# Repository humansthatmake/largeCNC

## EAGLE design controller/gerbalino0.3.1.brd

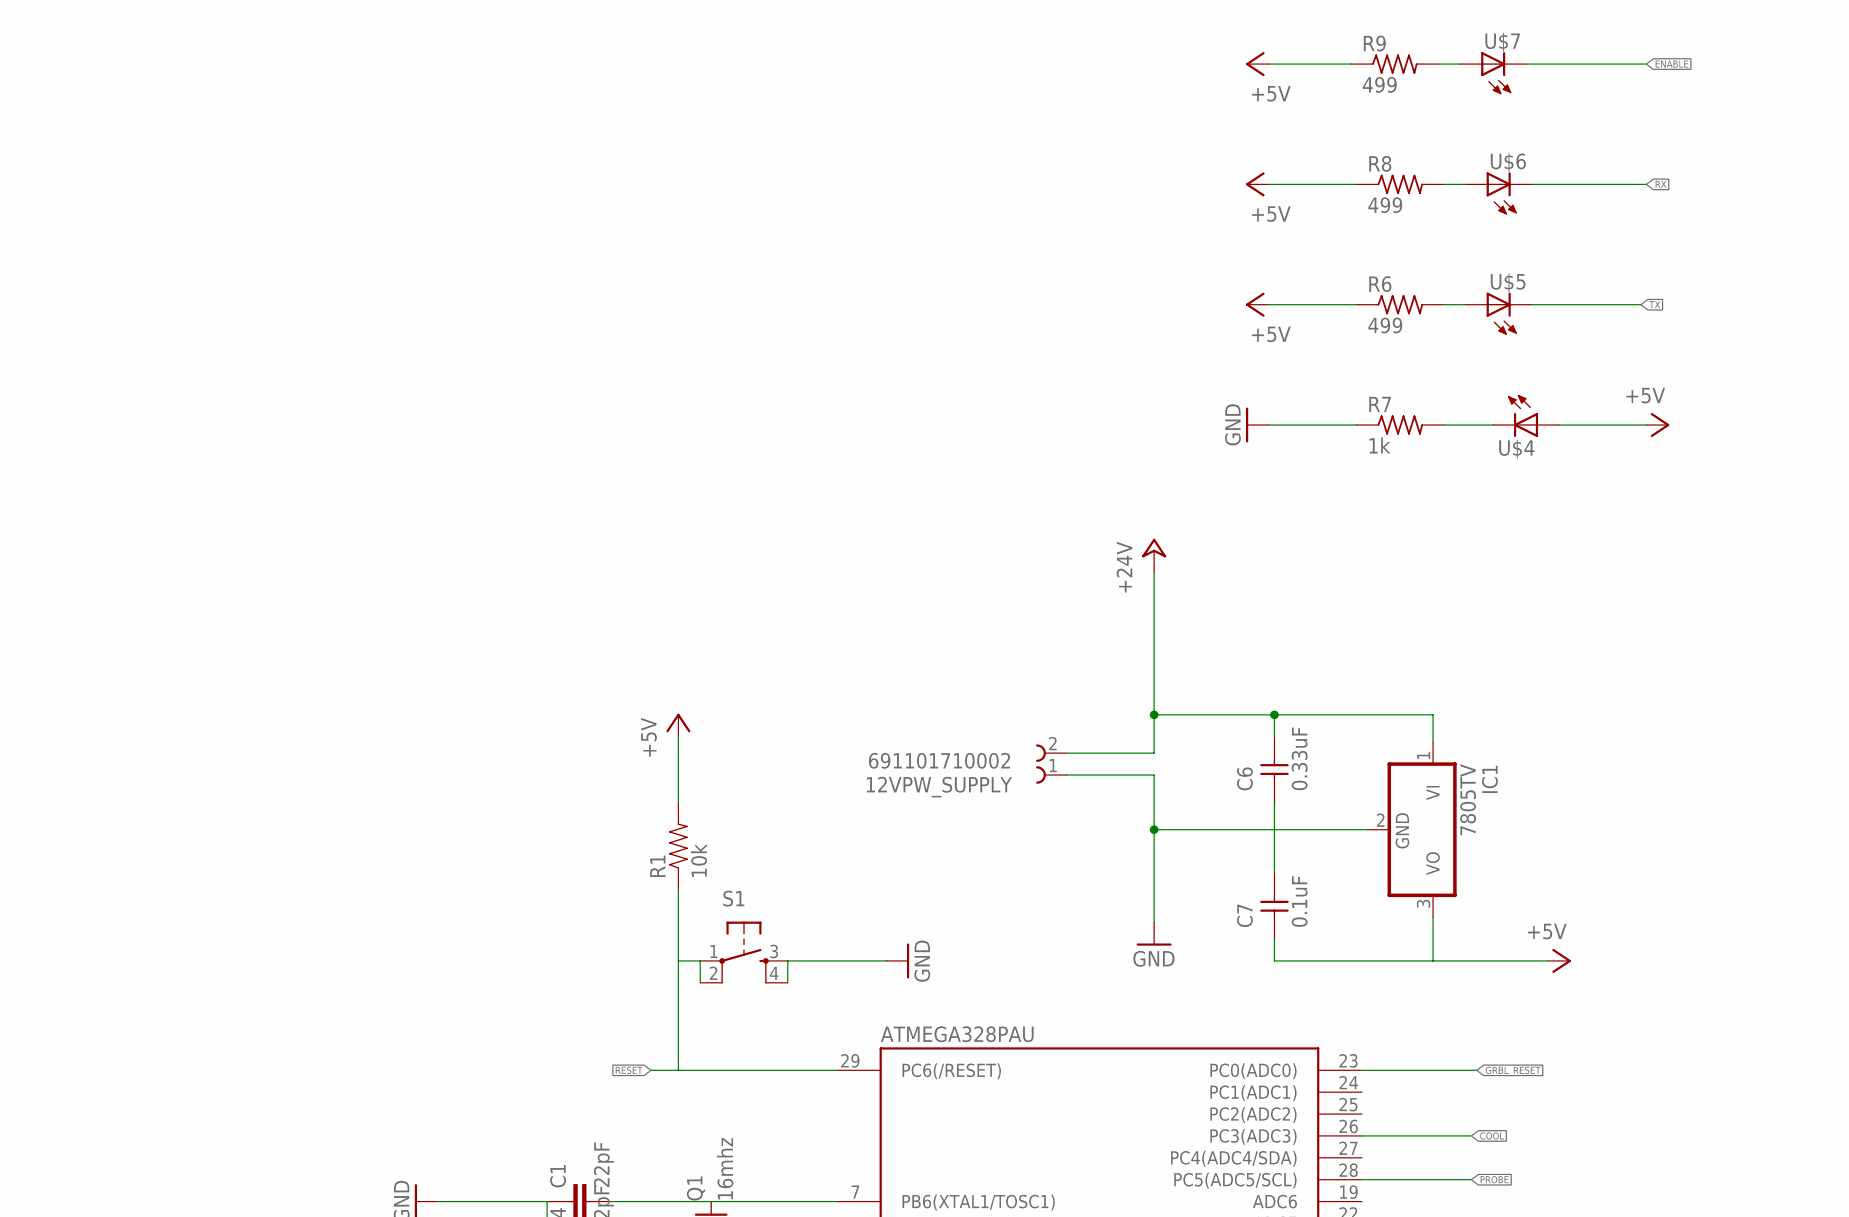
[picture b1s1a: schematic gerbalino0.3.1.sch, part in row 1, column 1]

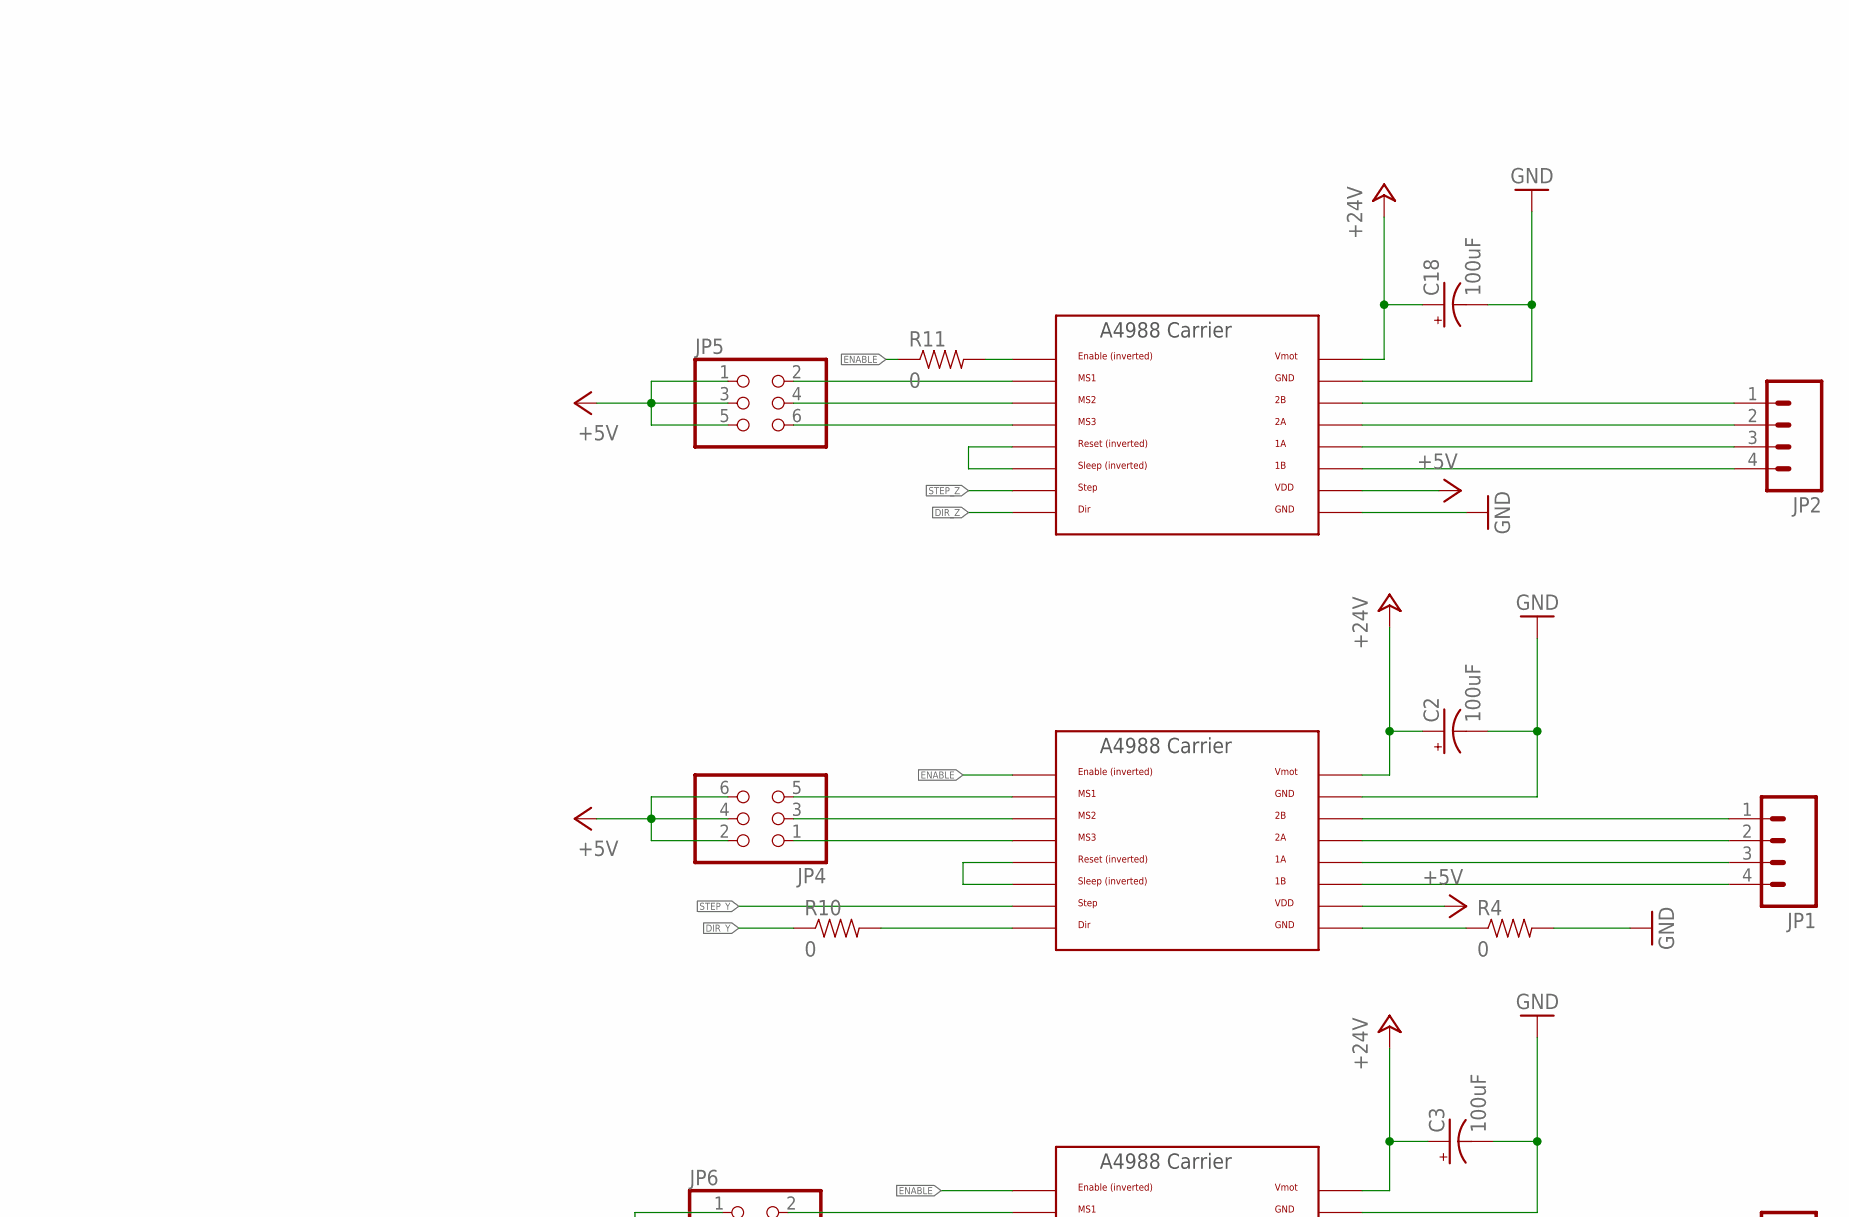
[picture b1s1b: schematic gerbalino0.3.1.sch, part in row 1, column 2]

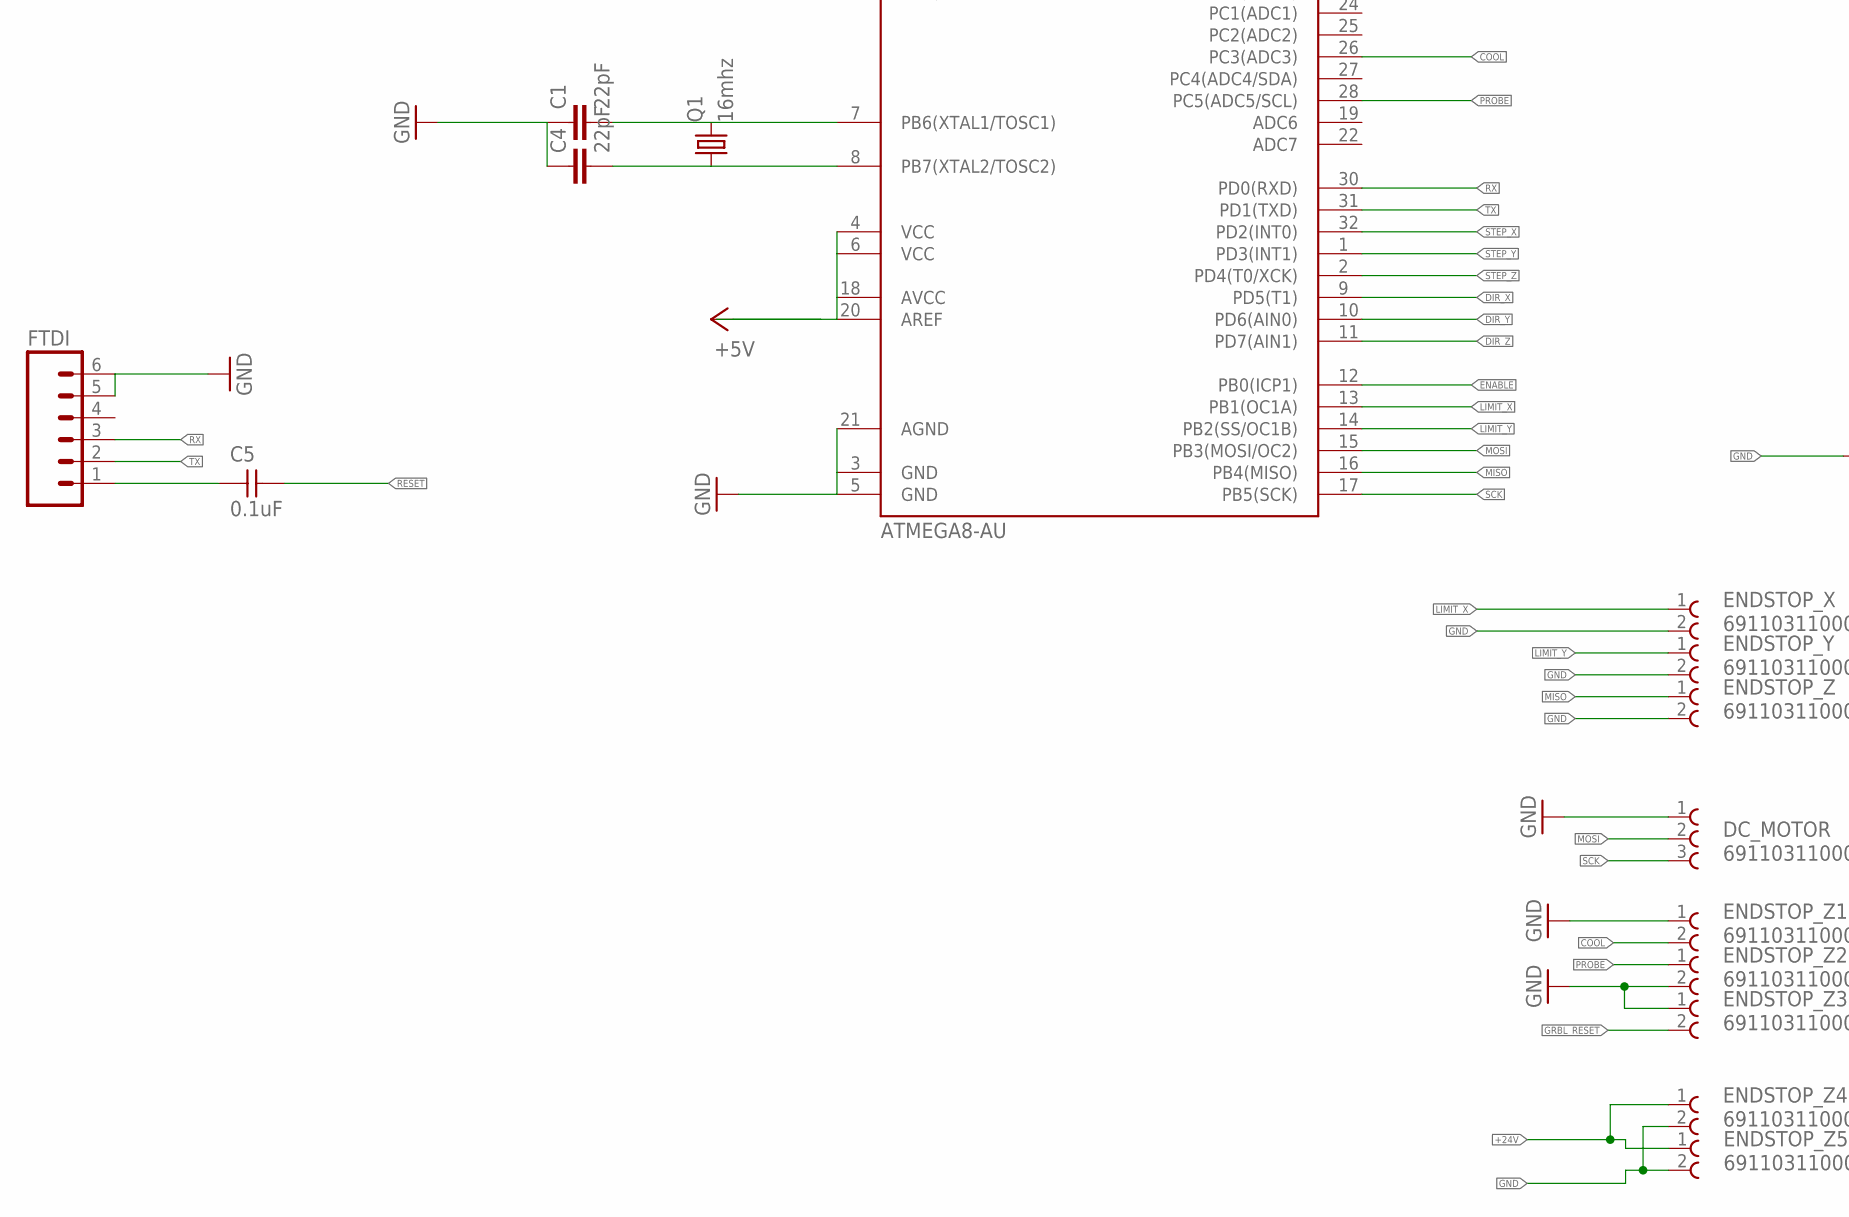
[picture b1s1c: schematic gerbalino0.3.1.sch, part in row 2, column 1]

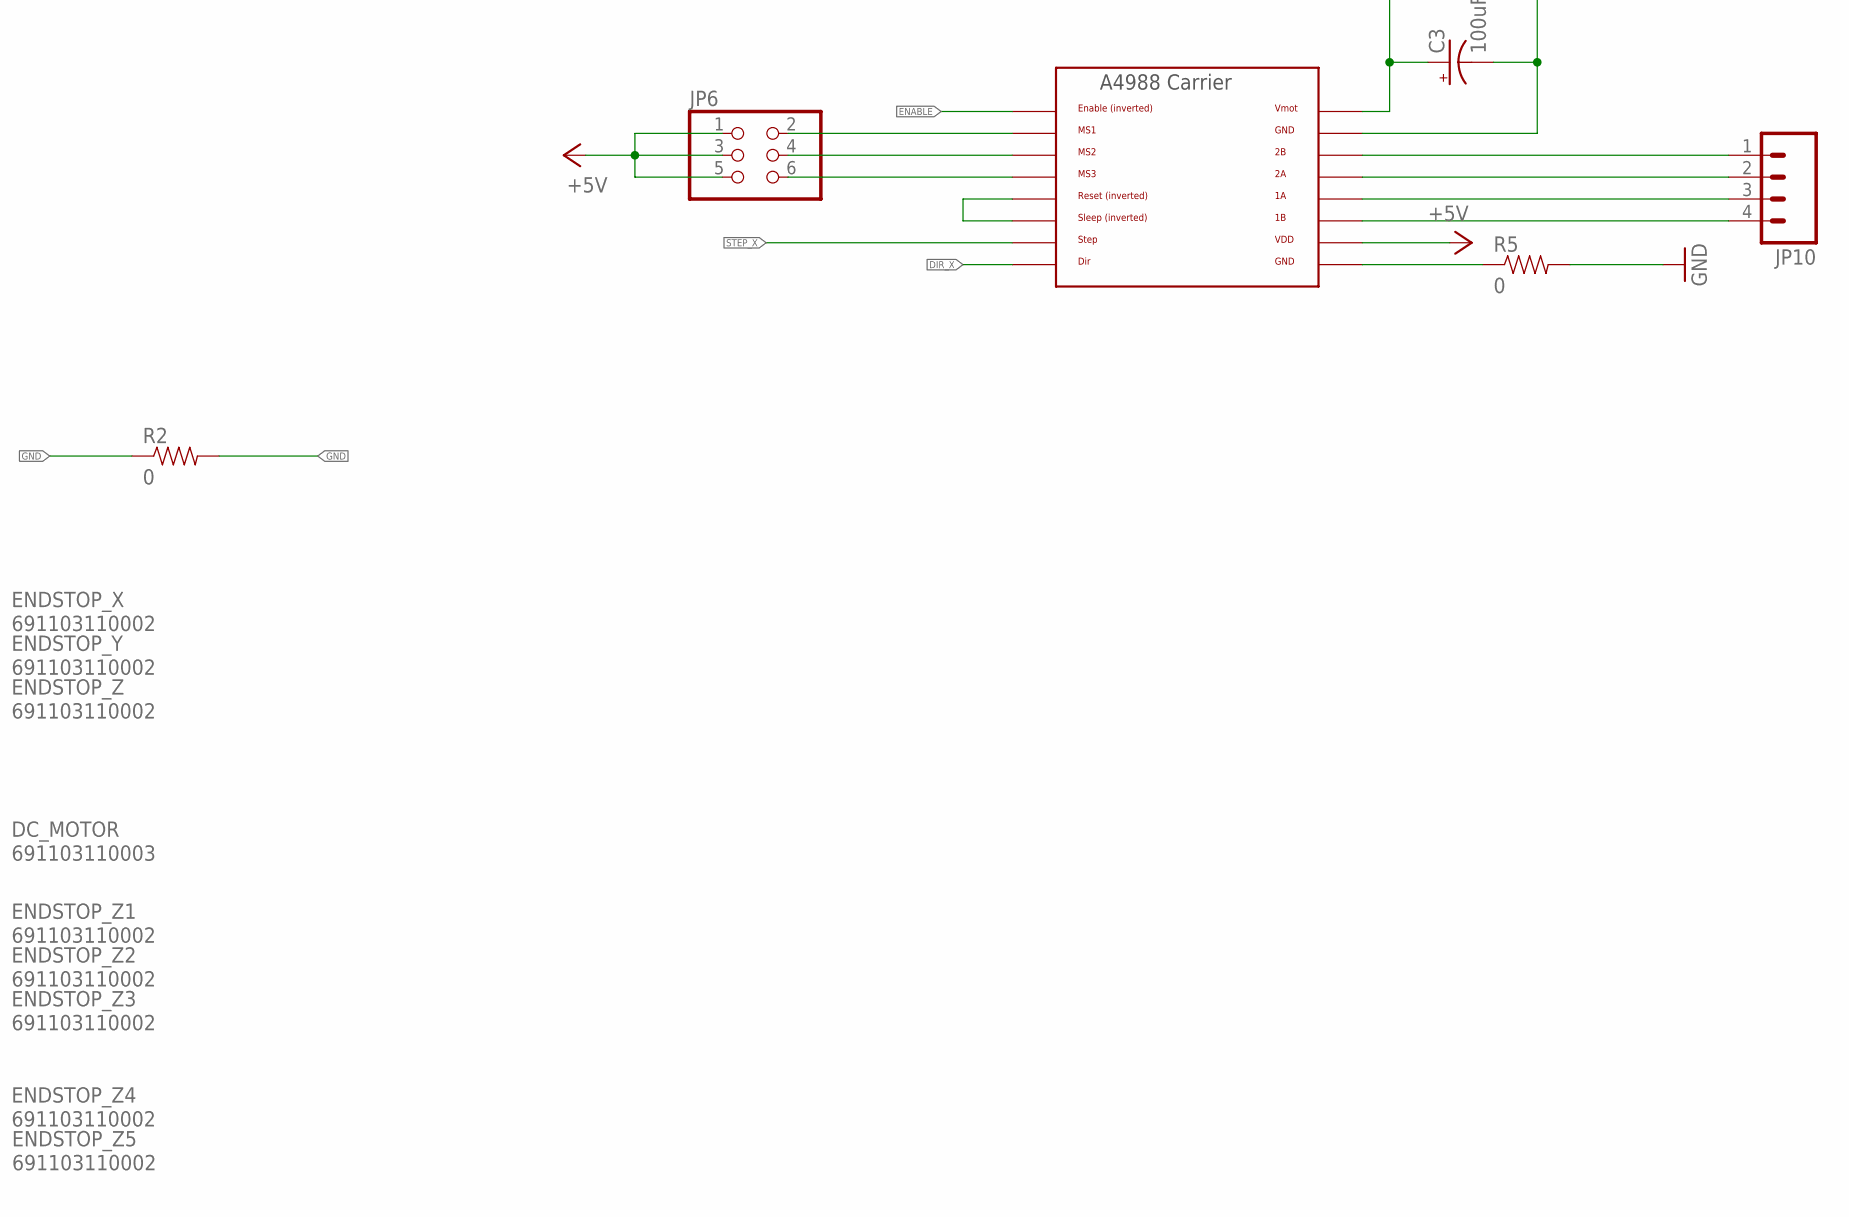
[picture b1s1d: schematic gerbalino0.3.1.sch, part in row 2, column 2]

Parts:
12VPW_SUPPLY: 691101710002
ATMEGA328PAU: ATMEGA8-AU; TQFP32-08
C1, C4: 22pF; 1206
C2, C3, C18: 100uF; UD-10X10_NICHICON
C5, C7: 0.1uF; 1206
C6: 0.33uF; 1206
DC_MOTOR: 691103110003
ENDSTOP_X: 691103110002
ENDSTOP_Y: 691103110002
ENDSTOP_Z, ENDSTOP_Z1, ENDSTOP_Z2, ENDSTOP_Z3, ENDSTOP_Z4, ENDSTOP_Z5: 691103110002
FTDI: M06SMD; 1X06-SMD
IC1: 7805TV; TO220V
JP1, JP2, JP10: M04LONGPADS; 1X04_LONGPADS
JP4, JP5, JP6: PINHD-2X3-SMD; 2X03SMD
Q1: 16mhz; CSM-7X-DU
R1: 10k; 1206
R2, R4, R5, R10, R11: 0; 1206
R6, R8, R9: 499; 1206
R7: 1k; 1206
S1: 6MM_SWITCH6MM_SWITCH; 6MM_SWITCH
U$1, U$2, U$3: POLOLU_A4983CARRIER; A4988BREAKOUT
U$4, U$5, U$6, U$7: LED1206; 1206

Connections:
+5V: ATMEGA328PAU.4 (VCC), ATMEGA328PAU.6 (VCC), ATMEGA328PAU.18 (AVCC), ATMEGA328PAU.20 (AREF), C7.1, IC1.3 (VO), JP4.2, JP4.4, JP4.6, JP5.1, JP5.3, JP5.5, JP6.1, JP6.3, JP6.5, R1.2, R6.1, R8.1, R9.1, U$1.VDD, U$2.VDD, U$3.VDD, U$4.1 (A)
+24V: 12VPW_SUPPLY.2, C2.+, C3.+, C6.2, C18.+, ENDSTOP_Z4.1, ENDSTOP_Z5.1, IC1.1 (VI), U$1.VMOT, U$2.VMOT, U$3.VMOT
COOL: ATMEGA328PAU.26 (PC3(ADC3)), ENDSTOP_Z1.2
DIR_X: ATMEGA328PAU.9 (PD5(T1)), U$3.DIR
DIR_Y: ATMEGA328PAU.10 (PD6(AIN0)), R10.1
DIR_Z: ATMEGA328PAU.11 (PD7(AIN1)), U$2.DIR
ENABLE: ATMEGA328PAU.12 (PB0(ICP1)), R11.1, R11.2, U$1.EN, U$2.EN, U$3.EN, U$7.2 (C)
GND: 12VPW_SUPPLY.1, ATMEGA328PAU.3 (GND), ATMEGA328PAU.5 (GND), ATMEGA328PAU.21 (AGND), C1.1, C2.-, C3.-, C4.1, C6.1, C7.2, C18.-, DC_MOTOR.1, ENDSTOP_X.2, ENDSTOP_Y.2, ENDSTOP_Z.2, ENDSTOP_Z1.1, ENDSTOP_Z2.2, ENDSTOP_Z3.1, ENDSTOP_Z4.2, ENDSTOP_Z5.2, FTDI.5, FTDI.6, IC1.2 (GND), R2.1, R2.2, R4.1, R4.2, R5.1, R5.2, R7.1, S1.3 (S), S1.4 (S1), U$1.GND, U$1.GND@0 (GND), U$2.GND, U$2.GND@0 (GND), U$3.GND, U$3.GND@0 (GND)
GRBL_RESET: ATMEGA328PAU.23 (PC0(ADC0)), ENDSTOP_Z3.2
LIMIT_X: ATMEGA328PAU.13 (PB1(OC1A)), ENDSTOP_X.1
LIMIT_Y: ATMEGA328PAU.14 (PB2(SS/OC1B)), ENDSTOP_Y.1
MISO: ATMEGA328PAU.16 (PB4(MISO)), ENDSTOP_Z.1
MOSI: ATMEGA328PAU.15 (PB3(MOSI/OC2)), DC_MOTOR.2
unnamed: R7.2, U$4.2 (C)
unnamed: C5.1, FTDI.1
unnamed: R8.2, U$6.1 (A)
unnamed: JP1.1, U$1.2B
unnamed: JP1.2, U$1.2A
unnamed: JP1.3, U$1.1A
unnamed: JP1.4, U$1.1B
unnamed: JP10.1, U$3.2B
unnamed: JP10.2, U$3.2A
unnamed: JP10.3, U$3.1A
unnamed: JP10.4, U$3.1B
unnamed: JP2.1, U$2.2B
unnamed: JP2.2, U$2.2A
unnamed: JP2.3, U$2.1A
unnamed: JP2.4, U$2.1B
unnamed: U$1.RST, U$1.SLP (SLEEP)
unnamed: U$3.RST, U$3.SLP (SLEEP)
unnamed: R9.2, U$7.1 (A)
unnamed: R10.2, U$1.DIR
unnamed: R6.2, U$5.1 (A)
unnamed: U$2.RST, U$2.SLP (SLEEP)
unnamed: ATMEGA328PAU.8 (PB7(XTAL2/TOSC2)), C4.2, Q1.1
unnamed: JP5.6, U$2.MS3
unnamed: JP5.4, U$2.MS2
unnamed: JP5.2, U$2.MS1
unnamed: JP4.1, U$1.MS3
unnamed: JP4.3, U$1.MS2
unnamed: JP4.5, U$1.MS1
unnamed: JP6.6, U$3.MS3
unnamed: JP6.4, U$3.MS2
unnamed: JP6.2, U$3.MS1
unnamed: ATMEGA328PAU.7 (PB6(XTAL1/TOSC1)), C1.2, Q1.2
PROBE: ATMEGA328PAU.28 (PC5(ADC5/SCL)), ENDSTOP_Z2.1
RESET: ATMEGA328PAU.29 (PC6(/RESET)), C5.2, R1.1, S1.1, S1.2 (P1)
RX: ATMEGA328PAU.30 (PD0(RXD)), FTDI.3, U$6.2 (C)
SCK: ATMEGA328PAU.17 (PB5(SCK)), DC_MOTOR.3
STEP_X: ATMEGA328PAU.32 (PD2(INT0)), U$3.STEP
STEP_Y: ATMEGA328PAU.1 (PD3(INT1)), U$1.STEP
STEP_Z: ATMEGA328PAU.2 (PD4(T0/XCK)), U$2.STEP
TX: ATMEGA328PAU.31 (PD1(TXD)), FTDI.2, U$5.2 (C)

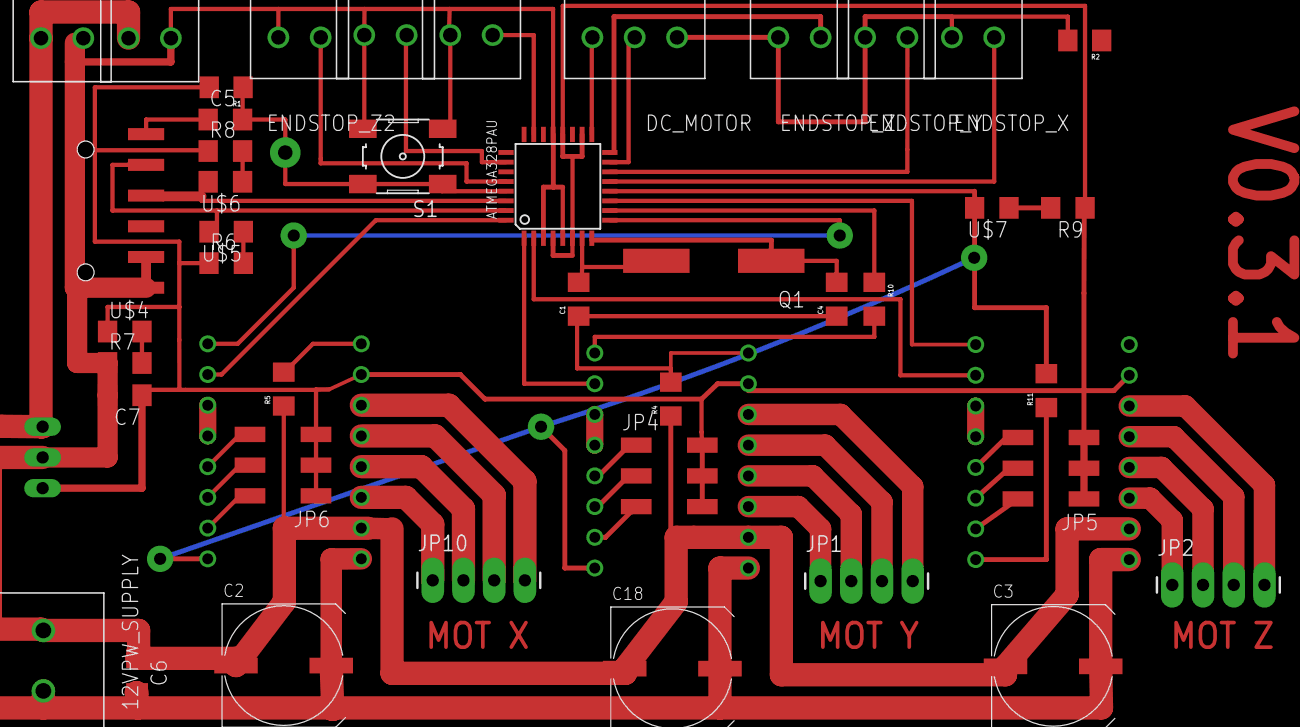
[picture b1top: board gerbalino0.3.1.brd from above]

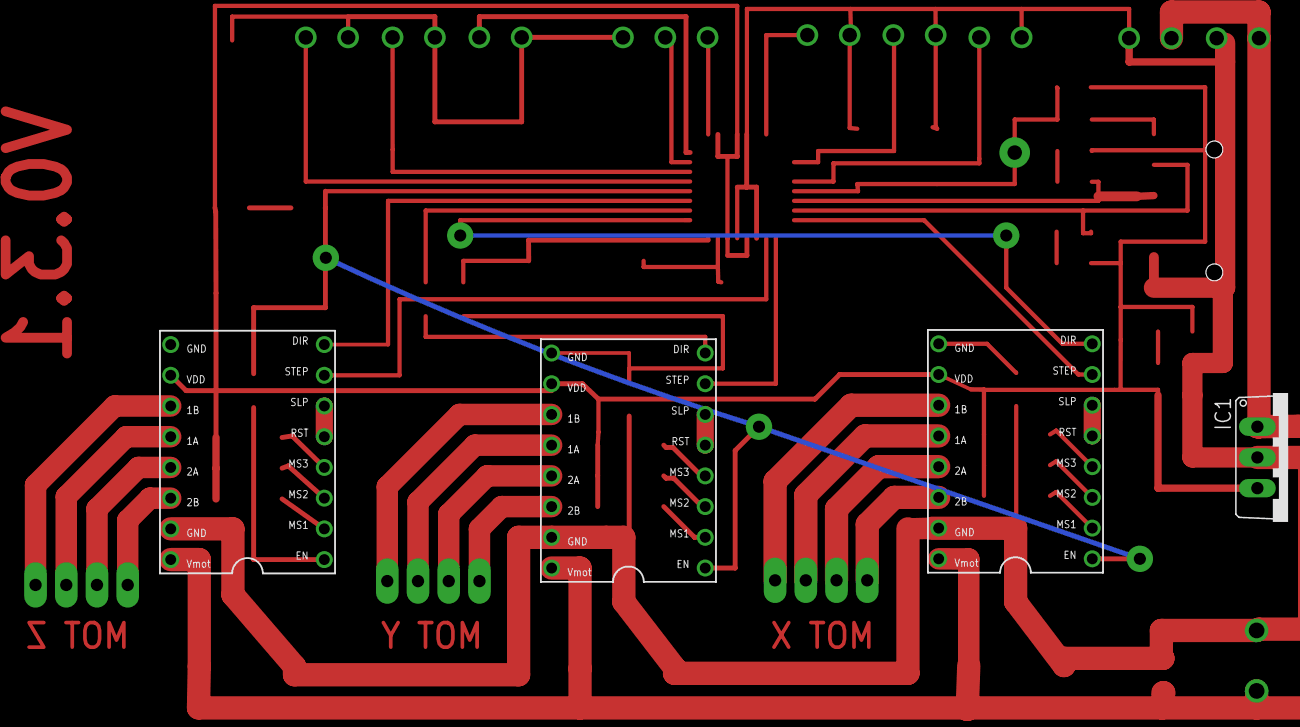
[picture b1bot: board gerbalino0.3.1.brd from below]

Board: 2 copper layers, 46 parts (4 on the bottom side), 53 nets.

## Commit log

2016-06-01 cnc controller first commit. moved gerbalino files to largeCNC

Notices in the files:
parts and their libraries:
Wurth_Elektronik_Electromechanic_Termina: Copyright: Würth Elektronik
01_SparkFun: Licensing: CC v3.0 Share-Alike You are welcome to use this library for commercial purposes.
